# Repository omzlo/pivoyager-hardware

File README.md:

# Pivoyager Hardware
Hardware design files for the PiVoyager

See https://www.omzlo.com/articles/pivoyager-the-smart-ups-for-the-raspberry-pi

## License

All hardware is licensed under [Creative Commons Attribution-ShareAlike 4.0 International (CC BY-SA 4.0)](https://creativecommons.org/licenses/by-sa/4.0/)

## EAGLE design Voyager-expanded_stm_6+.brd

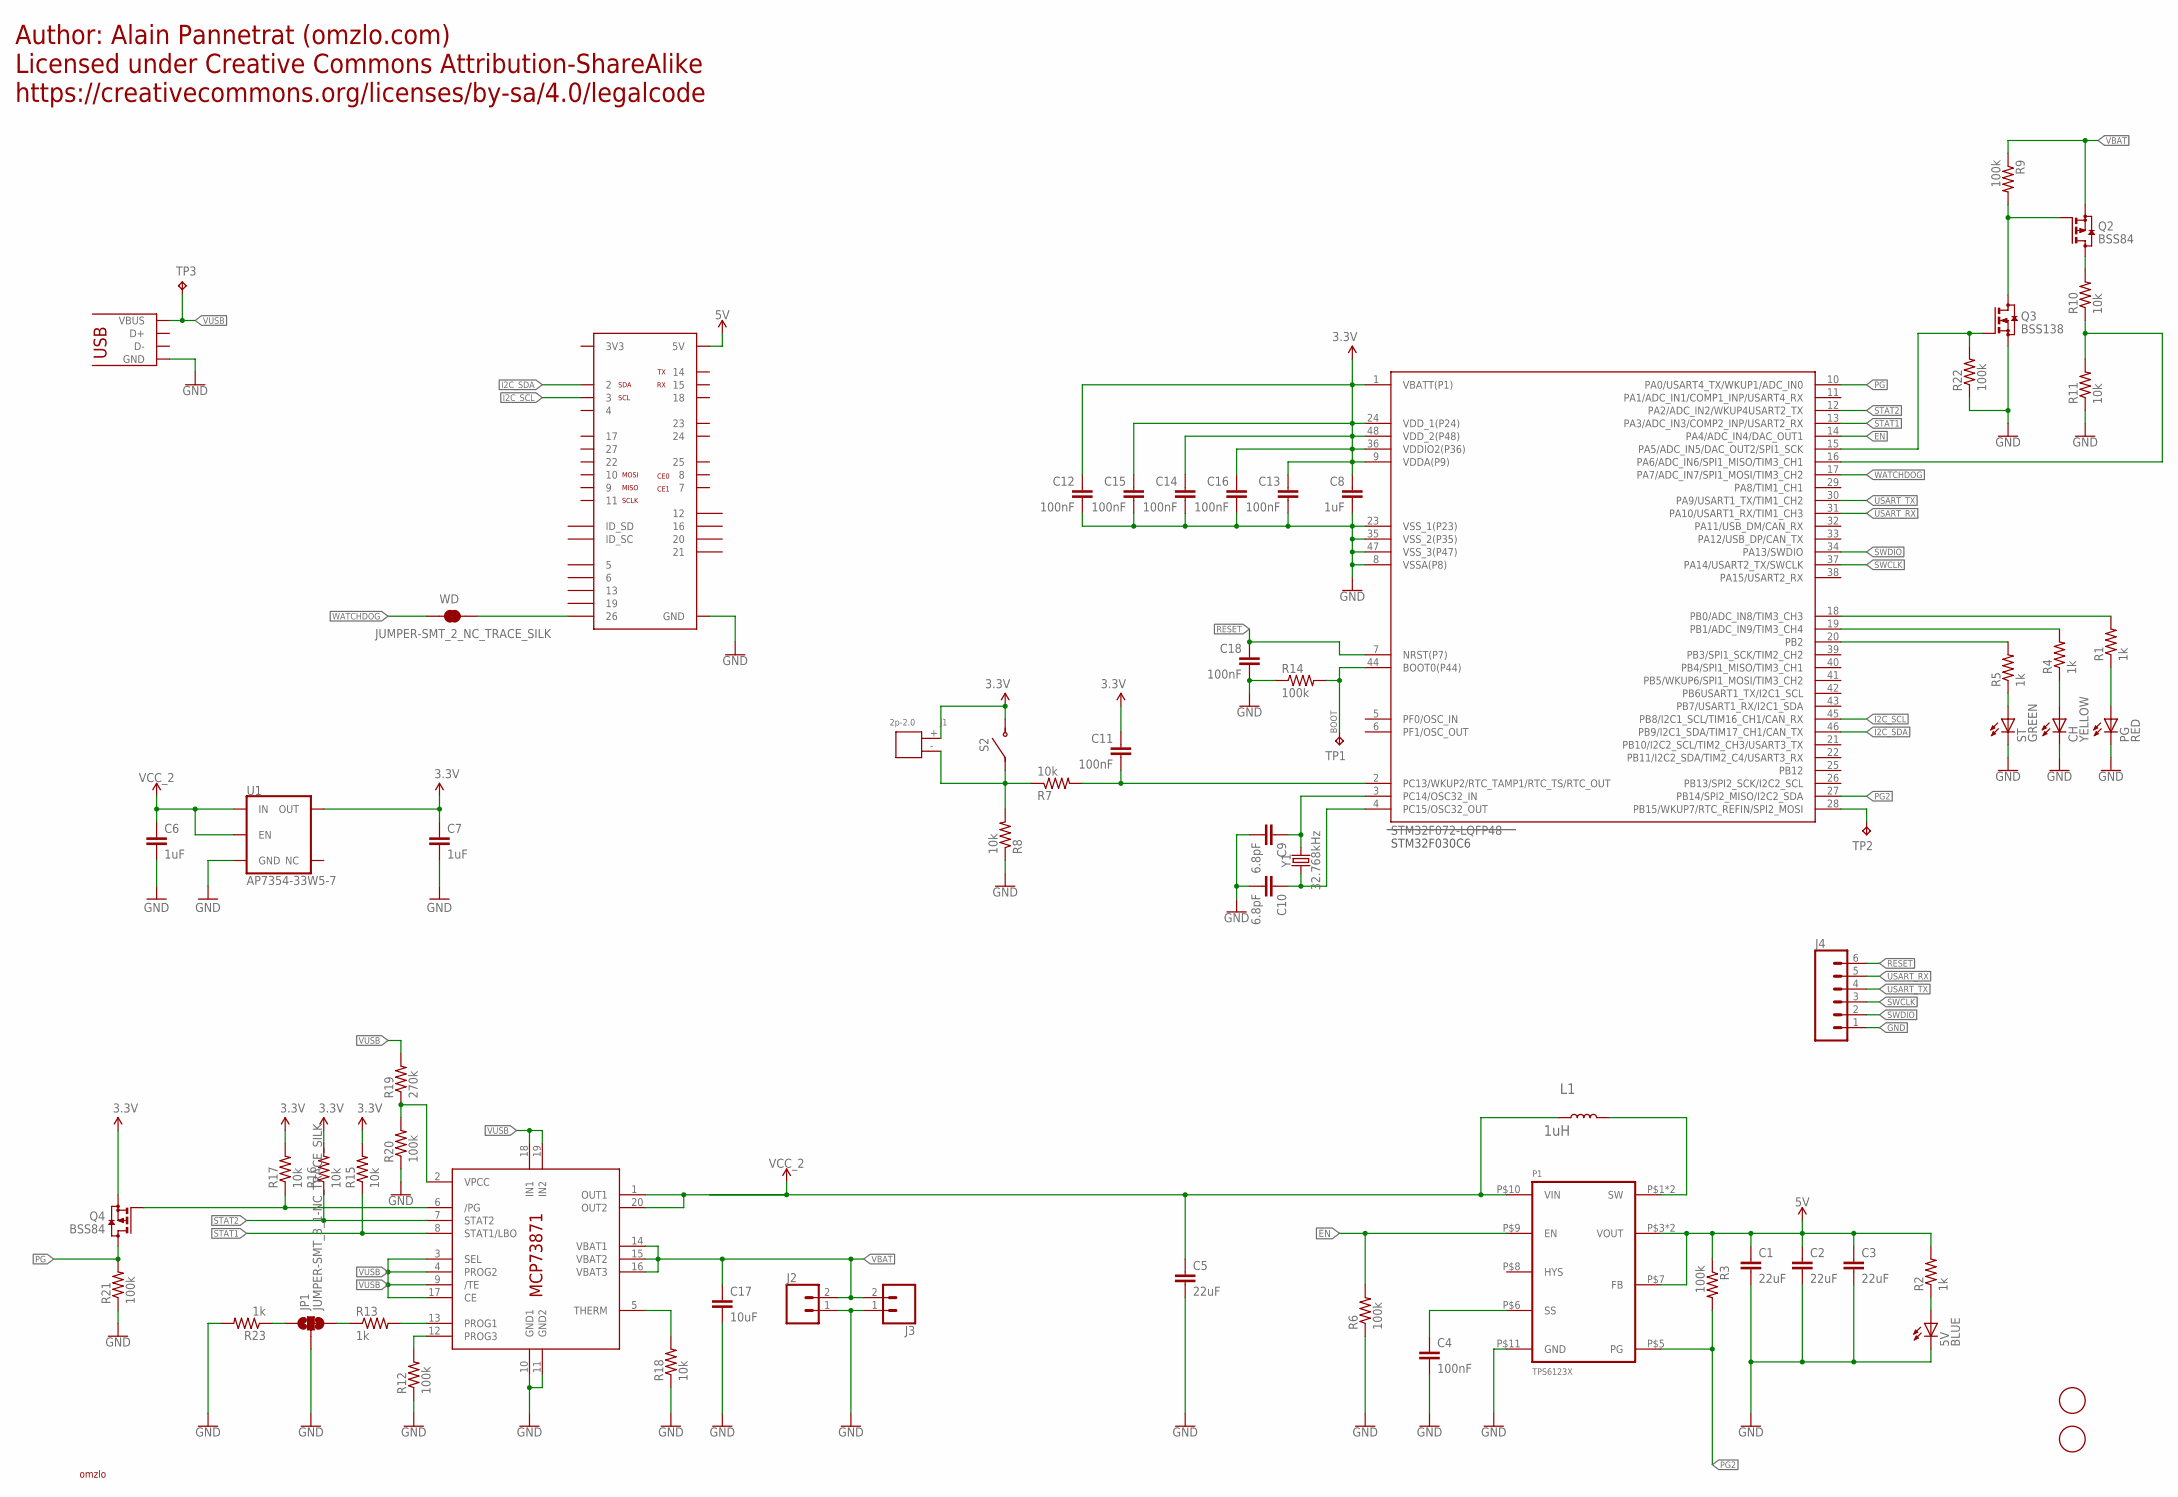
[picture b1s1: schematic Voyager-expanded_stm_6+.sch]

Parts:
5V: BLUE; CHIP-LED0805
C1, C2, C3, C5: 22uF; C1206
C4, C11, C12, C13, C14, C15, C16, C18: 100nF; C0603
C6, C7, C8: 1uF; 0805
C9, C10: 6.8pF; C0603
C17: 10uF; C0805
CH: YELLOW; CHIP-LED0805
IC1: MCP73871; QFN20
J1: 2p-2.0; H2-2.0-6X4.5MM
J2: CONN_021X02_NO_SILK; 1X02_NO_SILK
J3: CONN_02-JST-2MM-SMT; JST-2-SMD
J4: CONN_06NO_SILK_FEMALE_PTH; 1X06_NO_SILK
JP1: JUMPER-SMT_3_1-NC_TRACE_SILK; SMT-JUMPER_3_1-NC_TRACE_SILK
L1: 1uH; L5040S
P1: TPS6123X; PVSON-10
PG: RED; CHIP-LED0805
Q2, Q4: BSS84; SOT23
Q3: BSS138; SOT23
R1, R2, R4, R5, R13, R23: 1k; R0603
R3, R6, R9, R12, R14, R20, R21, R22: 100k; R0603
R7, R8, R10, R11, R15, R16, R17, R18: 10k; R0603
R19: 270k; R0603
S2: TACT-SWITCH; ALPS-SKSCPDE010
ST: GREEN; CHIP-LED0805
TP1, TP2, TP3: TPB1,27; B1,27
U1: AP7354-33W5-7; SOT23-5
U$1: RASPBERRY-PI-GPIO; 2X20
U$2: STM32F072-LQFP48; LQFP48
U$3: USB-MICROB
U$4, U$9: FIDUCIAL; FIDUCIAL_1MM
U$6: OMZLO
WD: JUMPER-SMT_2_NC_TRACE_SILK; SMT-JUMPER_2_NC_TRACE_SILK
Y1: 32.768kHz; CRYSTAL-SMD-3.2X1.5MM

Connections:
3.3V: C7.1, C8.1, C11.1, C12.1, C13.1, C14.1, C15.1, C16.1, J1.+, Q4.2 (S), R15.2, R16.2, R17.2, S2.P$3, S2.P$4, U1.5 (OUT), U$2.1 (VBATT(P1)), U$2.9 (VDDA(P9)), U$2.24 (VDD_1(P24)), U$2.36 (VDDIO2(P36)), U$2.48 (VDD_2(P48))
3V3: U$1.1 (3V3), U$1.17 (3V3)
5V: C1.1, C2.1, C3.1, P1.P$3 (VOUT), P1.P$4 (VOUT), P1.P$7 (FB), R2.2, R3.1, U$1.2 (5V), U$1.4 (5V)
BOOT: R14.2, TP1.TP, U$2.44 (BOOT0(P44))
EN: P1.P$9 (EN), R6.2, U$2.14 (PA4/ADC_IN4/DAC_OUT1)
GND: 5V.C, C1.2, C2.2, C3.2, C4.2, C5.2, C6.2, C7.2, C8.2, C9.2, C10.2, C12.2, C13.2, C14.2, C15.2, C16.2, C17.2, C18.2, CH.C, IC1.10 (GND1), IC1.11 (GND2), J2.1, J3.1 (2), J4.1, JP1.2, P1.P$11 (GND), PG.C, Q3.2 (S), R6.1, R8.1, R11.1, R12.1, R14.1, R18.1, R20.1, R21.1, R22.1, R23.2, ST.C, U1.2 (GND), U$1.6 (GND), U$1.9 (GND), U$1.14 (GND), U$1.20 (GND), U$1.25 (GND), U$1.30 (GND), U$1.34 (GND), U$1.39 (GND), U$2.8 (VSSA(P8)), U$2.23 (VSS_1(P23)), U$2.35 (VSS_2(P35)), U$2.47 (VSS_3(P47)), U$3.GND, U$3.MT1 (GND), U$3.MT2 (GND), U$3.P$1 (GND), U$3.P$2 (GND), U$3.P$3 (GND), U$3.P$4 (GND)
I2C_SCL: U$1.5 (3), U$2.45 (PB8/I2C1_SCL/TIM16_CH1/CAN_RX)
I2C_SDA: U$1.3 (2), U$2.46 (PB9/I2C1_SDA/TIM17_CH1/CAN_TX)
unnamed: C9.1, U$2.3 (PC14/OSC32_IN), Y1.P$2 (2)
unnamed: C10.1, U$2.4 (PC15/OSC32_OUT), Y1.P$1 (1)
unnamed: IC1.2 (VPCC), R19.1, R20.2
unnamed: R10.1, R11.2, U$2.16 (PA6/ADC_IN6/SPI1_MISO/TIM3_CH1)
unnamed: IC1.5 (THERM), R18.2
unnamed: IC1.12 (PROG3), R12.2
unnamed: IC1.13 (PROG1), R13.2
unnamed: R4.2, U$2.19 (PB1/ADC_IN9/TIM3_CH4)
unnamed: CH.A, R4.1
unnamed: R5.2, U$2.20 (PB2)
unnamed: Q2.3 (D), R10.2
unnamed: C4.1, P1.P$6 (SS)
unnamed: Q2.1 (G), Q3.3 (D), R9.2
unnamed: L1.2, P1.P$1 (SW), P1.P$2 (SW)
unnamed: R5.1, ST.A
unnamed: R1.2, U$2.18 (PB0/ADC_IN8/TIM3_CH3)
unnamed: 5V.A, R2.1
unnamed: TP2.TP, U$2.28 (PB15/WKUP7/RTC_REFIN/SPI2_MOSI)
unnamed: J1.-, R7.1, R8.2, S2.P$1, S2.P$2
unnamed: PG.A, R1.1
unnamed: U$1.37 (26), WD.2
unnamed: JP1.3, R13.1
unnamed: JP1.1, R23.1
PG: Q4.3 (D), R21.2, U$2.10 (PA0/USART4_TX/WKUP1/ADC_IN0)
PG2: P1.P$5 (PG), R3.2, U$2.27 (PB14/SPI2_MISO/I2C2_SDA)
PG_MCP: IC1.6 (/PG), Q4.1 (G), R17.1
RESET: C18.1, J4.6, U$2.7 (NRST(P7))
STAT1: IC1.8 (STAT1/LBO), R15.1, U$2.13 (PA3/ADC_IN3/COMP2_INP/USART2_RX)
STAT2: IC1.7 (STAT2), R16.1, U$2.12 (PA2/ADC_IN2/WKUP4USART2_TX)
SWCLK: J4.3, U$2.37 (PA14/USART2_TX/SWCLK)
SWDIO: J4.2, U$2.34 (PA13/SWDIO)
SWITCH: C11.2, R7.2, U$2.2 (PC13/WKUP2/RTC_TAMP1/RTC_TS/RTC_OUT)
USART_RX: J4.5, U$2.31 (PA10/USART1_RX/TIM1_CH3)
USART_TX: J4.4, U$2.30 (PA9/USART1_TX/TIM1_CH2)
VBAT: C17.1, IC1.14 (VBAT1), IC1.15 (VBAT2), IC1.16 (VBAT3), J2.2, J3.2 (1), Q2.2 (S), R9.1
VBAT_EN: Q3.1 (G), R22.2, U$2.15 (PA5/ADC_IN5/DAC_OUT2/SPI1_SCK)
VCC_2: C5.1, C6.1, IC1.1 (OUT1), IC1.20 (OUT2), L1.1, P1.P$10 (VIN), U1.1 (IN), U1.3 (EN)
VUSB: IC1.3 (SEL), IC1.4 (PROG2), IC1.9 (/TE), IC1.17 (CE), IC1.18 (IN1), IC1.19 (IN2), R19.2, TP3.TP, U$3.VBUS
WATCHDOG: U$2.17 (PA7/ADC_IN7/SPI1_MOSI/TIM3_CH2), WD.1

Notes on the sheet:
STM32F030C6
Author: Alain Pannetrat (omzlo.com) Licensed under Creative Commons Attribution-ShareAlike https://creativecommons.org/licenses/by-sa/4.0/legalcode

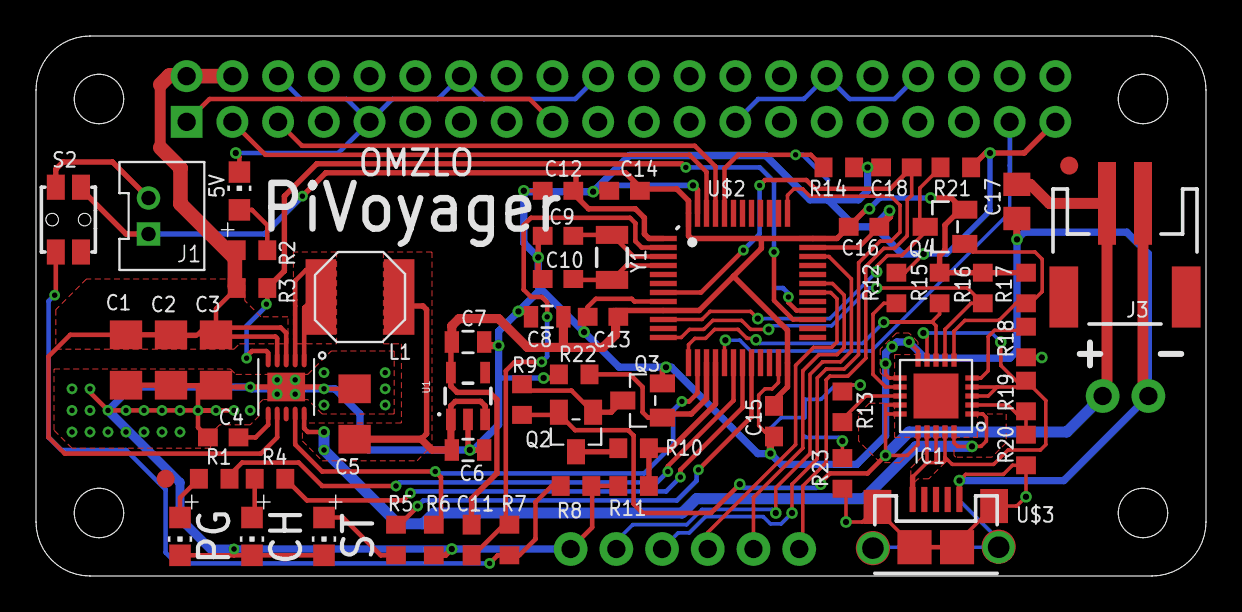
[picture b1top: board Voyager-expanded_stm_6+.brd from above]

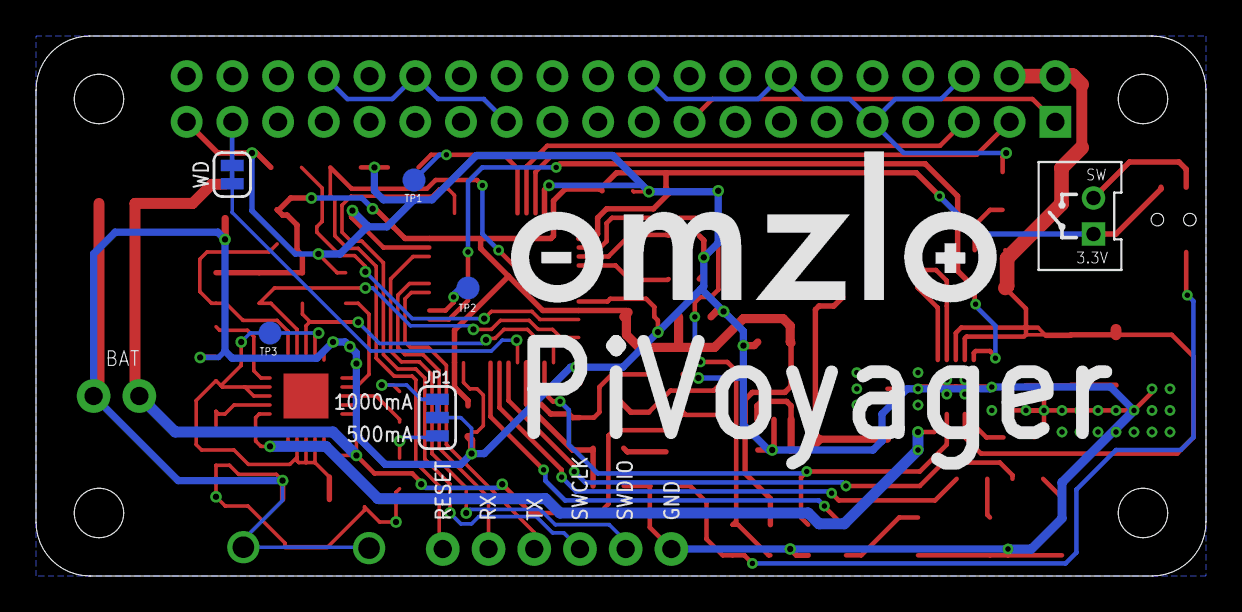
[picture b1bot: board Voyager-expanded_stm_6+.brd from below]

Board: 2 copper layers, 65.0 x 30.0 mm, 69 parts (6 on the bottom side), 47 nets.

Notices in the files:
parts and their libraries:
SparkFun-Capacitors: Licensing: Creative Commons ShareAlike 4.0 International - https://creativecommons.org/licenses/by-sa/4.0
pimoroni: Licensing: CC v3.0 Share-Alike You are welcome to use this library for commercial purposes.
